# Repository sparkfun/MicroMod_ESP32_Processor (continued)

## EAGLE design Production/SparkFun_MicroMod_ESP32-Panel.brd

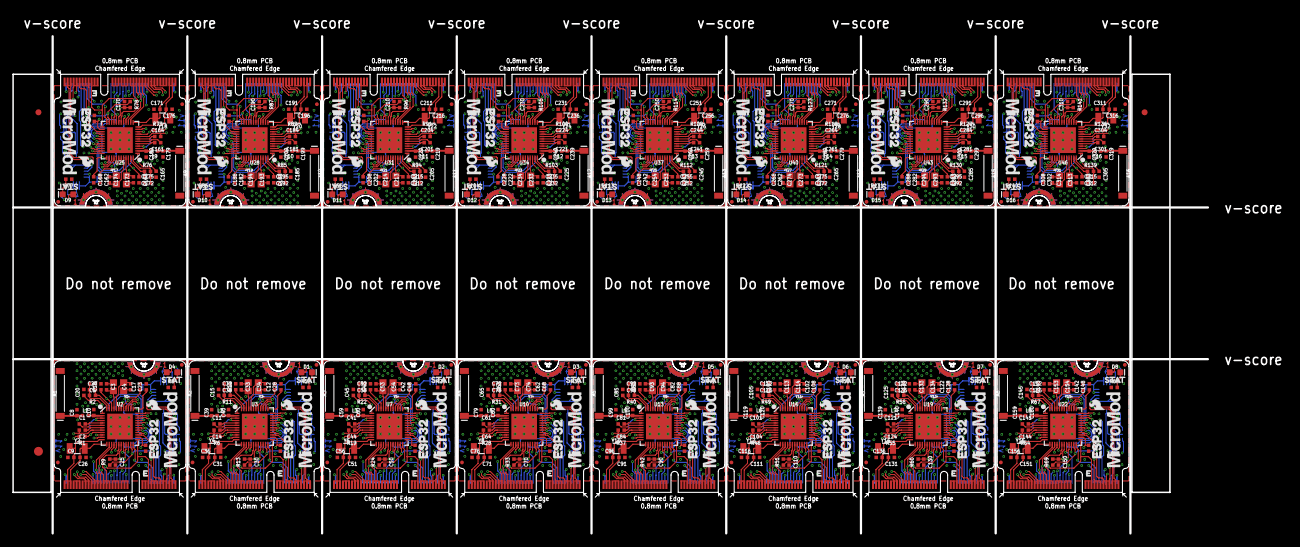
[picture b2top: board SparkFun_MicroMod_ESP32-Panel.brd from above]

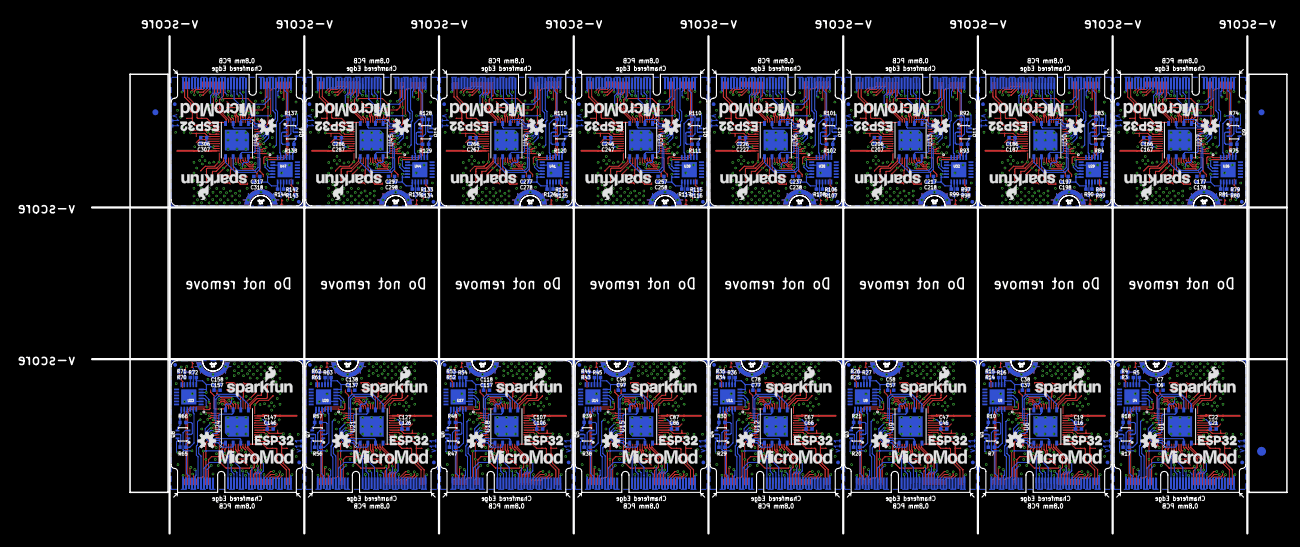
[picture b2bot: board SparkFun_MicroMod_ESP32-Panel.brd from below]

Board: 4 copper layers, 199.6 x 83.1 mm, 822 parts (291 on the bottom side), 864 nets.

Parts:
A1, A2, A3, A4, A5, A6, A7, A8, A9, A10, A11, A12, A13, A14, A15, A16: ANT-2.4GHZ-8.0X1.0MM
C1, C2, C11, C14, C41, C44, C61, C64, C81, C84, C101, C104, C121, C124, C141, C144, C161, C164, C181, C184, C201, C204, C221, C224, C241, C244, C261, C264, C281, C284, C301, C304: 270pF; 0402-TIGHT
C3, C4, C33, C34, C53, C54, C73, C74, C93, C94, C113, C114, C133, C134, C153, C154, C173, C174, C193, C194, C213, C214, C233, C234, C253, C254, C273, C274, C293, C294, C313, C314: 12pF; 0402-TIGHT
C5, C35, C55, C75, C95, C115, C135, C155, C175, C195, C215, C235, C255, C275, C295, C315: 10nF; 0402-TIGHT
C6, C12, C15, C16, C17, C20, C21, C23, C25, C28, C30, C37, C42, C45, C46, C48, C50, C57, C62, C65, C66, C68, C70, C77, C82, C85, C86, C88, C90, C97, C102, C105, C106, C108, C110, C117, C122, C125, C126, C128, C130, C137, C142, C145, C146, C148, C150, C157, C162, C165, C166, C168, C170, C177, C182, C185, C186, C188, C190, C197, C202, C205, C206, C208, C210, C217, C222, C225, C226, C228, C230, C237, C242, C245, C246, C248, C250, C257, C262, C265, C266, C268, C270, C277, C282, C285, C286, C288, C290, C297, C302, C305, C306, C308, C310, C317: 0.1uF; 0402-TIGHT
C7, C38, C58, C78, C98, C118, C138, C158, C178, C198, C218, C238, C258, C278, C298, C318: 4.7uF; 0402-TIGHT
C8, C10, C39, C40, C59, C60, C79, C80, C99, C100, C119, C120, C139, C140, C159, C160, C179, C180, C199, C200, C219, C220, C239, C240, C259, C260, C279, C280, C299, C300, C319, C320: DNP; 0402-TIGHT
C9, C26, C31, C36, C51, C56, C71, C76, C91, C96, C111, C116, C131, C136, C151, C156, C171, C176, C191, C196, C211, C216, C231, C236, C251, C256, C271, C276, C291, C296, C311, C316: 15pF; 0402-TIGHT
C13, C18, C43, C63, C83, C103, C123, C143, C163, C183, C203, C223, C243, C263, C283, C303: 100pF; 0402-TIGHT
C19, C22, C47, C67, C87, C107, C127, C147, C167, C187, C207, C227, C247, C267, C287, C307: 10uF; 0402-TIGHT
C24, C29, C49, C69, C89, C109, C129, C149, C169, C189, C209, C229, C249, C269, C289, C309: 1.0uF; 0402-TIGHT
C27, C32, C52, C72, C92, C112, C132, C152, C172, C192, C212, C232, C252, C272, C292, C312: 3.0nF; 0402-TIGHT
D1, D2, D3, D4, D5, D6, D7, D8, D9, D10, D11, D12, D13, D14, D15, D16: BLUE; LED-0603
E$1, E$2, E$3, E$4: FIDUCIAL-1X2
E$5, E$6: FIDUCIAL-1.5X3
FD1, FD2, FD3, FD4, FD5, FD6, FD7, FD8, FD9, FD10, FD11, FD12, FD13, FD14, FD15, FD16, FD17, FD18, FD19, FD20, FD21, FD22, FD23, FD24, FD25, FD26, FD27, FD28, FD29, FD30, FD31, FD32, FD33, FD34, FD35, FD36, FD37, FD38, FD39, FD40, FD41, FD42, FD43, FD44, FD45, FD46, FD47, FD48, FD49, FD50, FD51, FD52, FD53, FD54, FD55, FD56, FD57, FD58, FD59, FD60, FD61, FD62, FD63, FD64: FIDUCIALUFIDUCIAL; FIDUCIAL-MICRO
J1, J2, J3, J4, J5, J6, J7, J8, J9, J10, J11, J12, J13, J14, J15, J16: MICROMOD-2222; M.2-CARD-E-22
L1, L2, L3, L4, L5, L6, L7, L8, L9, L10, L11, L12, L13, L14, L15, L16: 0; 0402-TIGHT
LOGO1, LOGO2, LOGO5, LOGO7, LOGO9, LOGO11, LOGO13, LOGO15, LOGO17, LOGO19, LOGO21, LOGO23, LOGO25, LOGO27, LOGO29, LOGO31: SFE_LOGO_NAME_FLAME.1_INCH; SFE_LOGO_NAME_FLAME_.1
LOGO3, LOGO4, LOGO6, LOGO8, LOGO10, LOGO12, LOGO14, LOGO16, LOGO18, LOGO20, LOGO22, LOGO24, LOGO26, LOGO28, LOGO30, LOGO32: OSHW-LOGOS; OSHW-LOGO-S
Q1, Q2, Q3, Q4, Q5, Q6, Q7, Q8, Q9, Q10, Q11, Q12, Q13, Q14, Q15, Q16: MBT3904DW1T1; SC70-6
R1, R6, R7, R9, R10, R13, R17, R18, R19, R20, R21, R24, R28, R29, R30, R33, R37, R38, R39, R42, R46, R47, R48, R51, R55, R56, R57, R60, R64, R65, R66, R69, R73, R74, R75, R78, R82, R83, R84, R87, R91, R92, R93, R96, R100, R101, R102, R105, R109, R110, R111, R114, R118, R119, R120, R123, R127, R128, R129, R132, R136, R137, R138, R141: 10k; 0402-TIGHT
R2, R11, R22, R31, R40, R49, R58, R67, R76, R85, R94, R103, R112, R121, R130, R139: 20k; 0402-TIGHT
R3, R14, R25, R34, R43, R52, R61, R70, R79, R88, R97, R106, R115, R124, R133, R142: 22k; 0402-TIGHT
R4, R15, R26, R35, R44, R53, R62, R71, R80, R89, R98, R107, R116, R125, R134, R143: 33k; 0402-TIGHT
R5, R16, R27, R36, R45, R54, R63, R72, R81, R90, R99, R108, R117, R126, R135, R144: 2.2k; 0402-TIGHT
R8, R12, R23, R32, R41, R50, R59, R68, R77, R86, R95, R104, R113, R122, R131, R140: 1k; 0402-TIGHT
U1, U6, U9, U12, U15, U18, U21, U24, U27, U30, U33, U36, U39, U42, U45, U48: W25QXX128MBIT-6X5; WSON-8-6X5
U2, U3, U7, U10, U13, U16, U19, U22, U25, U28, U31, U34, U37, U40, U43, U46: ESP32; QFN48-0.4MM
U4, U5, U8, U11, U14, U17, U20, U23, U26, U29, U32, U35, U38, U41, U44, U47: CP210X; QFN24
U$1, U$5, U$13, U$19, U$25, U$31, U$37, U$43, U$49, U$55, U$61, U$67, U$73, U$79, U$85, U$91: STAT0
U$2, U$6, U$9, U$11, U$15, U$17, U$21, U$23, U$27, U$29, U$33, U$35, U$39, U$41, U$45, U$47, U$51, U$53, U$57, U$59, U$63, U$65, U$69, U$71, U$75, U$77, U$81, U$83, U$87, U$89, U$93, U$95: MICROMOD_LOGO_.5
U$3, U$7, U$8, U$12, U$14, U$18, U$20, U$24, U$26, U$30, U$32, U$36, U$38, U$42, U$44, U$48, U$50, U$54, U$56, U$60, U$62, U$66, U$68, U$72, U$74, U$78, U$80, U$84, U$86, U$90, U$92, U$96: ESP321
U$4, U$10, U$16, U$22, U$28, U$34, U$40, U$46, U$52, U$58, U$64, U$70, U$76, U$82, U$88, U$94: SFE_LOGO_FLAME_.1
Y1, Y3, Y5, Y7, Y9, Y11, Y13, Y15, Y17, Y19, Y21, Y23, Y25, Y27, Y29, Y31: 40MHz; CRYSTAL-SMD-2X2.5MM
Y2, Y4, Y6, Y8, Y10, Y12, Y14, Y16, Y18, Y20, Y22, Y24, Y26, Y28, Y30, Y32: 32.768kHz; CRYSTAL-SMD-3.2X1.5MM

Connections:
0-!BOOT!: J1.11, Q2.6, R9.1, U2.23
0-!BOOT!1: J2.11, Q1.6, R13.1, U3.23
0-!BOOT!2: J3.11, Q3.6, R24.1, U7.23
0-!BOOT!3: J4.11, Q4.6, R33.1, U10.23
0-!BOOT!4: J5.11, Q5.6, R42.1, U13.23
0-!BOOT!5: J6.11, Q6.6, R51.1, U16.23
0-!BOOT!6: J7.11, Q7.6, R60.1, U19.23
0-!BOOT!7: J8.11, Q8.6, R69.1, U22.23
0-!BOOT!8: J9.11, Q9.6, R78.1, U25.23
0-!BOOT!9: J10.11, Q10.6, R87.1, U28.23
0-!BOOT!10: J11.11, Q11.6, R96.1, U31.23
0-!BOOT!11: J12.11, Q12.6, R105.1, U34.23
0-!BOOT!12: J13.11, Q13.6, R114.1, U37.23
0-!BOOT!13: J14.11, Q14.6, R123.1, U40.23
0-!BOOT!14: J15.11, Q15.6, R132.1, U43.23
0-!BOOT!15: J16.11, Q16.6, R141.1, U46.23
1: C14.1, U3.7
2: C11.2, U3.5
2-STAT_LED: D4.A, U2.22
2-STAT_LED1: D1.A, U3.22
2-STAT_LED2: D2.A, U7.22
2-STAT_LED3: D3.A, U10.22
2-STAT_LED4: D5.A, U13.22
2-STAT_LED5: D6.A, U16.22
2-STAT_LED6: D7.A, U19.22
2-STAT_LED7: D8.A, U22.22
2-STAT_LED8: D9.A, U25.22
2-STAT_LED9: D10.A, U28.22
2-STAT_LED10: D11.A, U31.22
2-STAT_LED11: D12.A, U34.22
2-STAT_LED12: D13.A, U37.22
2-STAT_LED13: D14.A, U40.22
2-STAT_LED14: D15.A, U43.22
2-STAT_LED15: D16.A, U46.22
3: C11.1, U3.6
3.3V: C6.1, C7.1, C18.1, C20.1, C21.1, C22.1, C23.1, C25.1, J1.2, J1.74, R1.2, R5.2, R9.2, U2.1, U2.3, U2.4, U2.19, U2.37, U2.43, U2.46, U4.5, U4.6, U4.7
3.3V1: C13.1, C15.1, C16.1, C19.1, C28.1, C30.1, C37.1, C38.1, J2.2, J2.74, R6.2, R13.2, R16.2, U3.1, U3.3, U3.4, U3.19, U3.37, U3.43, U3.46, U5.5, U5.6, U5.7
3.3V2: C43.1, C45.1, C46.1, C47.1, C48.1, C50.1, C57.1, C58.1, J3.2, J3.74, R19.2, R24.2, R27.2, U7.1, U7.3, U7.4, U7.19, U7.37, U7.43, U7.46, U8.5, U8.6, U8.7
3.3V3: C63.1, C65.1, C66.1, C67.1, C68.1, C70.1, C77.1, C78.1, J4.2, J4.74, R28.2, R33.2, R36.2, U10.1, U10.3, U10.4, U10.19, U10.37, U10.43, U10.46, U11.5, U11.6, U11.7
3.3V4: C83.1, C85.1, C86.1, C87.1, C88.1, C90.1, C97.1, C98.1, J5.2, J5.74, R37.2, R42.2, R45.2, U13.1, U13.3, U13.4, U13.19, U13.37, U13.43, U13.46, U14.5, U14.6, U14.7
3.3V5: C103.1, C105.1, C106.1, C107.1, C108.1, C110.1, C117.1, C118.1, J6.2, J6.74, R46.2, R51.2, R54.2, U16.1, U16.3, U16.4, U16.19, U16.37, U16.43, U16.46, U17.5, U17.6, U17.7
3.3V6: C123.1, C125.1, C126.1, C127.1, C128.1, C130.1, C137.1, C138.1, J7.2, J7.74, R55.2, R60.2, R63.2, U19.1, U19.3, U19.4, U19.19, U19.37, U19.43, U19.46, U20.5, U20.6, U20.7
3.3V7: C143.1, C145.1, C146.1, C147.1, C148.1, C150.1, C157.1, C158.1, J8.2, J8.74, R64.2, R69.2, R72.2, U22.1, U22.3, U22.4, U22.19, U22.37, U22.43, U22.46, U23.5, U23.6, U23.7
3.3V8: C163.1, C165.1, C166.1, C167.1, C168.1, C170.1, C177.1, C178.1, J9.2, J9.74, R73.2, R78.2, R81.2, U25.1, U25.3, U25.4, U25.19, U25.37, U25.43, U25.46, U26.5, U26.6, U26.7
3.3V9: C183.1, C185.1, C186.1, C187.1, C188.1, C190.1, C197.1, C198.1, J10.2, J10.74, R82.2, R87.2, R90.2, U28.1, U28.3, U28.4, U28.19, U28.37, U28.43, U28.46, U29.5, U29.6, U29.7
3.3V10: C203.1, C205.1, C206.1, C207.1, C208.1, C210.1, C217.1, C218.1, J11.2, J11.74, R91.2, R96.2, R99.2, U31.1, U31.3, U31.4, U31.19, U31.37, U31.43, U31.46, U32.5, U32.6, U32.7
3.3V11: C223.1, C225.1, C226.1, C227.1, C228.1, C230.1, C237.1, C238.1, J12.2, J12.74, R100.2, R105.2, R108.2, U34.1, U34.3, U34.4, U34.19, U34.37, U34.43, U34.46, U35.5, U35.6, U35.7
3.3V12: C243.1, C245.1, C246.1, C247.1, C248.1, C250.1, C257.1, C258.1, J13.2, J13.74, R109.2, R114.2, R117.2, U37.1, U37.3, U37.4, U37.19, U37.37, U37.43, U37.46, U38.5, U38.6, U38.7
3.3V13: C263.1, C265.1, C266.1, C267.1, C268.1, C270.1, C277.1, C278.1, J14.2, J14.74, R118.2, R123.2, R126.2, U40.1, U40.3, U40.4, U40.19, U40.37, U40.43, U40.46, U41.5, U41.6, U41.7
3.3V14: C283.1, C285.1, C286.1, C287.1, C288.1, C290.1, C297.1, C298.1, J15.2, J15.74, R127.2, R132.2, R135.2, U43.1, U43.3, U43.4, U43.19, U43.37, U43.43, U43.46, U44.5, U44.6, U44.7
3.3V15: C303.1, C305.1, C306.1, C307.1, C308.1, C310.1, C317.1, C318.1, J16.2, J16.74, R136.2, R141.2, R144.2, U46.1, U46.3, U46.4, U46.19, U46.37, U46.43, U46.46, U47.5, U47.6, U47.7
4: C44.1, U7.7
4-I2C_!INT: J1.16, U2.24
4-I2C_!INT1: J2.16, U3.24
4-I2C_!INT2: J3.16, U7.24
4-I2C_!INT3: J4.16, U10.24
4-I2C_!INT4: J5.16, U13.24
4-I2C_!INT5: J6.16, U16.24
4-I2C_!INT6: J7.16, U19.24
4-I2C_!INT7: J8.16, U22.24
4-I2C_!INT8: J9.16, U25.24
4-I2C_!INT9: J10.16, U28.24
4-I2C_!INT10: J11.16, U31.24
4-I2C_!INT11: J12.16, U34.24
4-I2C_!INT12: J13.16, U37.24
4-I2C_!INT13: J14.16, U40.24
4-I2C_!INT14: J15.16, U43.24
4-I2C_!INT15: J16.16, U46.24
5: C41.2, U7.5
5-!CS: J1.55, U2.34
5-!CS1: J2.55, U3.34
5-!CS2: J3.55, U7.34
5-!CS3: J4.55, U10.34
5-!CS4: J5.55, U13.34
5-!CS5: J6.55, U16.34
5-!CS6: J7.55, U19.34
5-!CS7: J8.55, U22.34
5-!CS8: J9.55, U25.34
5-!CS9: J10.55, U28.34
5-!CS10: J11.55, U31.34
5-!CS11: J12.55, U34.34
5-!CS12: J13.55, U37.34
5-!CS13: J14.55, U40.34
5-!CS14: J15.55, U43.34
5-!CS15: J16.55, U46.34
6: C41.1, U7.6
7: C64.1, U10.7
8: C61.2, U10.5
9: C61.1, U10.6
10: C84.1, U13.7
11: C81.2, U13.5
12: C81.1, U13.6
12-PWM1: J1.47, U2.18
12-PWM2: J2.47, U3.18
12-PWM3: J3.47, U7.18
12-PWM4: J4.47, U10.18
12-PWM5: J5.47, U13.18
12-PWM6: J6.47, U16.18
12-PWM7: J7.47, U19.18
12-PWM8: J8.47, U22.18
12-PWM9: J9.47, U25.18
12-PWM10: J10.47, U28.18
12-PWM11: J11.47, U31.18
12-PWM12: J12.47, U34.18
12-PWM13: J13.47, U37.18
12-PWM14: J14.47, U40.18
12-PWM15: J15.47, U43.18
12-PWM16: J16.47, U46.18
13: C104.1, U16.7
13-PWM0: J1.32, U2.20
13-PWM1: J2.32, U3.20
13-PWM2: J3.32, U7.20
13-PWM3: J4.32, U10.20
13-PWM4: J5.32, U13.20
13-PWM5: J6.32, U16.20
13-PWM6: J7.32, U19.20
13-PWM7: J8.32, U22.20
13-PWM8: J9.32, U25.20
13-PWM9: J10.32, U28.20
13-PWM10: J11.32, U31.20
13-PWM11: J12.32, U34.20
13-PWM12: J13.32, U37.20
13-PWM13: J14.32, U40.20
13-PWM14: J15.32, U43.20
13-PWM15: J16.32, U46.20
14: C101.2, U16.5
14-D0: J1.10, U2.17
14-D1: J2.10, U3.17
14-D2: J3.10, U7.17
14-D3: J4.10, U10.17
14-D4: J5.10, U13.17
14-D5: J6.10, U16.17
14-D6: J7.10, U19.17
14-D7: J8.10, U22.17
14-D8: J9.10, U25.17
14-D9: J10.10, U28.17
14-D10: J11.10, U31.17
14-D11: J12.10, U34.17
14-D12: J13.10, U37.17
14-D13: J14.10, U40.17
14-D14: J15.10, U43.17
14-D15: J16.10, U46.17
15: C101.1, U16.6
15-G0: J1.40, U2.21
15-G1: J2.40, U3.21
15-G2: J3.40, U7.21
15-G3: J4.40, U10.21
15-G4: J5.40, U13.21
15-G5: J6.40, U16.21
15-G6: J7.40, U19.21
15-G7: J8.40, U22.21
15-G8: J9.40, U25.21
15-G9: J10.40, U28.21
15-G10: J11.40, U31.21
15-G11: J12.40, U34.21
15-G12: J13.40, U37.21
15-G13: J14.40, U40.21
15-G14: J15.40, U43.21
15-G15: J16.40, U46.21
16: C124.1, U19.7
16-G4/RX1/AUD_IN: J1.19, J1.48, J1.54, U2.25
16-G4/RX1/AUD_IN1: J2.19, J2.48, J2.54, U3.25
16-G4/RX1/AUD_IN2: J3.19, J3.48, J3.54, U7.25
16-G4/RX1/AUD_IN3: J4.19, J4.48, J4.54, U10.25
16-G4/RX1/AUD_IN4: J5.19, J5.48, J5.54, U13.25
16-G4/RX1/AUD_IN5: J6.19, J6.48, J6.54, U16.25
16-G4/RX1/AUD_IN6: J7.19, J7.48, J7.54, U19.25
16-G4/RX1/AUD_IN7: J8.19, J8.48, J8.54, U22.25
16-G4/RX1/AUD_IN8: J9.19, J9.48, J9.54, U25.25
16-G4/RX1/AUD_IN9: J10.19, J10.48, J10.54, U28.25
16-G4/RX1/AUD_IN10: J11.19, J11.48, J11.54, U31.25
16-G4/RX1/AUD_IN11: J12.19, J12.48, J12.54, U34.25
16-G4/RX1/AUD_IN12: J13.19, J13.48, J13.54, U37.25
16-G4/RX1/AUD_IN13: J14.19, J14.48, J14.54, U40.25
16-G4/RX1/AUD_IN14: J15.19, J15.48, J15.54, U43.25
16-G4/RX1/AUD_IN15: J16.19, J16.48, J16.54, U46.25
17: C121.2, U19.5
17-G3/TX1/AUD_OUT: J1.17, J1.46, J1.56, U2.27
17-G3/TX1/AUD_OUT1: J2.17, J2.46, J2.56, U3.27
17-G3/TX1/AUD_OUT2: J3.17, J3.46, J3.56, U7.27
17-G3/TX1/AUD_OUT3: J4.17, J4.46, J4.56, U10.27
17-G3/TX1/AUD_OUT4: J5.17, J5.46, J5.56, U13.27
17-G3/TX1/AUD_OUT5: J6.17, J6.46, J6.56, U16.27
17-G3/TX1/AUD_OUT6: J7.17, J7.46, J7.56, U19.27
17-G3/TX1/AUD_OUT7: J8.17, J8.46, J8.56, U22.27
17-G3/TX1/AUD_OUT8: J9.17, J9.46, J9.56, U25.27
17-G3/TX1/AUD_OUT9: J10.17, J10.46, J10.56, U28.27
17-G3/TX1/AUD_OUT10: J11.17, J11.46, J11.56, U31.27
17-G3/TX1/AUD_OUT11: J12.17, J12.46, J12.56, U34.27
17-G3/TX1/AUD_OUT12: J13.17, J13.46, J13.56, U37.27
17-G3/TX1/AUD_OUT13: J14.17, J14.46, J14.56, U40.27
17-G3/TX1/AUD_OUT14: J15.17, J15.46, J15.56, U43.27
17-G3/TX1/AUD_OUT15: J16.17, J16.46, J16.56, U46.27
18: C121.1, U19.6
18-SCK: J1.57, U2.35
18-SCK1: J2.57, U3.35
18-SCK2: J3.57, U7.35
18-SCK3: J4.57, U10.35
18-SCK4: J5.57, U13.35
18-SCK5: J6.57, U16.35
18-SCK6: J7.57, U19.35
18-SCK7: J8.57, U22.35
18-SCK8: J9.57, U25.35
18-SCK9: J10.57, U28.35
18-SCK10: J11.57, U31.35
18-SCK11: J12.57, U34.35
18-SCK12: J13.57, U37.35
18-SCK13: J14.57, U40.35
18-SCK14: J15.57, U43.35
18-SCK15: J16.57, U46.35
19: C144.1, U22.7
19-CIPO: J1.61, U2.38
19-CIPO1: J2.61, U3.38
19-CIPO2: J3.61, U7.38
19-CIPO3: J4.61, U10.38
19-CIPO4: J5.61, U13.38
19-CIPO5: J6.61, U16.38
19-CIPO6: J7.61, U19.38
19-CIPO7: J8.61, U22.38
19-CIPO8: J9.61, U25.38
19-CIPO9: J10.61, U28.38
19-CIPO10: J11.61, U31.38
19-CIPO11: J12.61, U34.38
19-CIPO12: J13.61, U37.38
19-CIPO13: J14.61, U40.38
19-CIPO14: J15.61, U43.38
19-CIPO15: J16.61, U46.38
20: C141.2, U22.5
21: C141.1, U22.6
21-SDA: J1.12, U2.42
21-SDA1: J2.12, U3.42
21-SDA2: J3.12, U7.42
21-SDA3: J4.12, U10.42
21-SDA4: J5.12, U13.42
21-SDA5: J6.12, U16.42
21-SDA6: J7.12, U19.42
21-SDA7: J8.12, U22.42
21-SDA8: J9.12, U25.42
21-SDA9: J10.12, U28.42
21-SDA10: J11.12, U31.42
21-SDA11: J12.12, U34.42
21-SDA12: J13.12, U37.42
21-SDA13: J14.12, U40.42
21-SDA14: J15.12, U43.42
21-SDA15: J16.12, U46.42
22: C164.1, U25.7
22-SCL: J1.14, U2.39
22-SCL1: J2.14, U3.39
22-SCL2: J3.14, U7.39
22-SCL3: J4.14, U10.39
22-SCL4: J5.14, U13.39
22-SCL5: J6.14, U16.39
22-SCL6: J7.14, U19.39
22-SCL7: J8.14, U22.39
22-SCL8: J9.14, U25.39
22-SCL9: J10.14, U28.39
22-SCL10: J11.14, U31.39
22-SCL11: J12.14, U34.39
22-SCL12: J13.14, U37.39
22-SCL13: J14.14, U40.39
22-SCL14: J15.14, U43.39
22-SCL15: J16.14, U46.39
23: C161.2, U25.5
23-COPI: J1.59, U2.36
23-COPI1: J2.59, U3.36
23-COPI2: J3.59, U7.36
23-COPI3: J4.59, U10.36
23-COPI4: J5.59, U13.36
23-COPI5: J6.59, U16.36
23-COPI6: J7.59, U19.36
23-COPI7: J8.59, U22.36
23-COPI8: J9.59, U25.36
23-COPI9: J10.59, U28.36
23-COPI10: J11.59, U31.36
23-COPI11: J12.59, U34.36
23-COPI12: J13.59, U37.36
23-COPI13: J14.59, U40.36
23-COPI14: J15.59, U43.36
23-COPI15: J16.59, U46.36
24: C161.1, U25.6
25: C184.1, U28.7
25-G1/AUD_LRCLK/SCL1: J1.42, J1.52, J1.53, U2.14
25-G1/AUD_LRCLK/SCL2: J2.42, J2.52, J2.53, U3.14
25-G1/AUD_LRCLK/SCL3: J3.42, J3.52, J3.53, U7.14
25-G1/AUD_LRCLK/SCL4: J4.42, J4.52, J4.53, U10.14
25-G1/AUD_LRCLK/SCL5: J5.42, J5.52, J5.53, U13.14
25-G1/AUD_LRCLK/SCL6: J6.42, J6.52, J6.53, U16.14
25-G1/AUD_LRCLK/SCL7: J7.42, J7.52, J7.53, U19.14
25-G1/AUD_LRCLK/SCL8: J8.42, J8.52, J8.53, U22.14
25-G1/AUD_LRCLK/SCL9: J9.42, J9.52, J9.53, U25.14
25-G1/AUD_LRCLK/SCL10: J10.42, J10.52, J10.53, U28.14
25-G1/AUD_LRCLK/SCL11: J11.42, J11.52, J11.53, U31.14
25-G1/AUD_LRCLK/SCL12: J12.42, J12.52, J12.53, U34.14
25-G1/AUD_LRCLK/SCL13: J13.42, J13.52, J13.53, U37.14
25-G1/AUD_LRCLK/SCL14: J14.42, J14.52, J14.53, U40.14
25-G1/AUD_LRCLK/SCL15: J15.42, J15.52, J15.53, U43.14
25-G1/AUD_LRCLK/SCL16: J16.42, J16.52, J16.53, U46.14
26: C181.2, U28.5
26-G2/AUD_BCLK/SDA1: J1.44, J1.50, J1.51, U2.15
26-G2/AUD_BCLK/SDA2: J2.44, J2.50, J2.51, U3.15
26-G2/AUD_BCLK/SDA3: J3.44, J3.50, J3.51, U7.15
26-G2/AUD_BCLK/SDA4: J4.44, J4.50, J4.51, U10.15
26-G2/AUD_BCLK/SDA5: J5.44, J5.50, J5.51, U13.15
26-G2/AUD_BCLK/SDA6: J6.44, J6.50, J6.51, U16.15
26-G2/AUD_BCLK/SDA7: J7.44, J7.50, J7.51, U19.15
26-G2/AUD_BCLK/SDA8: J8.44, J8.50, J8.51, U22.15
26-G2/AUD_BCLK/SDA9: J9.44, J9.50, J9.51, U25.15
26-G2/AUD_BCLK/SDA10: J10.44, J10.50, J10.51, U28.15
26-G2/AUD_BCLK/SDA11: J11.44, J11.50, J11.51, U31.15
26-G2/AUD_BCLK/SDA12: J12.44, J12.50, J12.51, U34.15
26-G2/AUD_BCLK/SDA13: J13.44, J13.50, J13.51, U37.15
26-G2/AUD_BCLK/SDA14: J14.44, J14.50, J14.51, U40.15
26-G2/AUD_BCLK/SDA15: J15.44, J15.50, J15.51, U43.15
26-G2/AUD_BCLK/SDA16: J16.44, J16.50, J16.51, U46.15
27: C181.1, U28.6
27-D1: J1.18, U2.16
27-D2: J2.18, U3.16
27-D3: J3.18, U7.16
27-D4: J4.18, U10.16
27-D5: J5.18, U13.16
27-D6: J6.18, U16.16
27-D7: J7.18, U19.16
27-D8: J8.18, U22.16
27-D9: J9.18, U25.16
27-D10: J10.18, U28.16
27-D11: J11.18, U31.16
27-D12: J12.18, U34.16
27-D13: J13.18, U37.16
27-D14: J14.18, U40.16
27-D15: J15.18, U43.16
27-D16: J16.18, U46.16
28: C204.1, U31.7
29: C201.2, U31.5
30: C201.1, U31.6
31: C224.1, U34.7
32: C221.2, U34.5
32-G5/RTC: C9.2, J1.73, U2.12, Y2.P$1
32-G5/RTC1: C36.2, J2.73, U3.12, Y4.P$1
32-G5/RTC2: C56.2, J3.73, U7.12, Y6.P$1
32-G5/RTC3: C76.2, J4.73, U10.12, Y8.P$1
32-G5/RTC4: C96.2, J5.73, U13.12, Y10.P$1
32-G5/RTC5: C116.2, J6.73, U16.12, Y12.P$1
32-G5/RTC6: C136.2, J7.73, U19.12, Y14.P$1
32-G5/RTC7: C156.2, J8.73, U22.12, Y16.P$1
32-G5/RTC8: C176.2, J9.73, U25.12, Y18.P$1
32-G5/RTC9: C196.2, J10.73, U28.12, Y20.P$1
32-G5/RTC10: C216.2, J11.73, U31.12, Y22.P$1
32-G5/RTC11: C236.2, J12.73, U34.12, Y24.P$1
32-G5/RTC12: C256.2, J13.73, U37.12, Y26.P$1
32-G5/RTC13: C276.2, J14.73, U40.12, Y28.P$1
32-G5/RTC14: C296.2, J15.73, U43.12, Y30.P$1
32-G5/RTC15: C316.2, J16.73, U46.12, Y32.P$1
33: C221.1, U34.6
33-G6/RTC: C26.2, J1.71, U2.13, Y2.P$2
33-G6/RTC1: C31.2, J2.71, U3.13, Y4.P$2
33-G6/RTC2: C51.2, J3.71, U7.13, Y6.P$2
33-G6/RTC3: C71.2, J4.71, U10.13, Y8.P$2
33-G6/RTC4: C91.2, J5.71, U13.13, Y10.P$2
33-G6/RTC5: C111.2, J6.71, U16.13, Y12.P$2
33-G6/RTC6: C131.2, J7.71, U19.13, Y14.P$2
33-G6/RTC7: C151.2, J8.71, U22.13, Y16.P$2
33-G6/RTC8: C171.2, J9.71, U25.13, Y18.P$2
33-G6/RTC9: C191.2, J10.71, U28.13, Y20.P$2
33-G6/RTC10: C211.2, J11.71, U31.13, Y22.P$2
33-G6/RTC11: C231.2, J12.71, U34.13, Y24.P$2
33-G6/RTC12: C251.2, J13.71, U37.13, Y26.P$2
33-G6/RTC13: C271.2, J14.71, U40.13, Y28.P$2
33-G6/RTC14: C291.2, J15.71, U43.13, Y30.P$2
33-G6/RTC15: C311.2, J16.71, U46.13, Y32.P$2
34: C244.1, U37.7
34-A0: J1.34, U2.10
34-A1: J2.34, U3.10
34-A2: J3.34, U7.10
34-A3: J4.34, U10.10
34-A4: J5.34, U13.10
34-A5: J6.34, U16.10
34-A6: J7.34, U19.10
34-A7: J8.34, U22.10
34-A8: J9.34, U25.10
34-A9: J10.34, U28.10
34-A10: J11.34, U31.10
34-A11: J12.34, U34.10
34-A12: J13.34, U37.10
34-A13: J14.34, U40.10
34-A14: J15.34, U43.10
34-A15: J16.34, U46.10
35: C241.2, U37.5
35-A1: J1.38, U2.11
35-A2: J2.38, U3.11
35-A3: J3.38, U7.11
35-A4: J4.38, U10.11
35-A5: J5.38, U13.11
35-A6: J6.38, U16.11
35-A7: J7.38, U19.11
35-A8: J8.38, U22.11
35-A9: J9.38, U25.11
35-A10: J10.38, U28.11
35-A11: J11.38, U31.11
35-A12: J12.38, U34.11
35-A13: J13.38, U37.11
35-A14: J14.38, U40.11
35-A15: J15.38, U43.11
35-A16: J16.38, U46.11
36: C1.2, U2.5
37: C1.1, U2.6
38: C2.1, U2.7
39: C241.1, U37.6
39-BATT/1: C14.2, J2.49, U3.8
39-BATT/2: C44.2, J3.49, U7.8
39-BATT/3: C2.2, J1.49, U2.8
39-BATT/4: C64.2, J4.49, U10.8
39-BATT/5: C84.2, J5.49, U13.8
39-BATT/6: C104.2, J6.49, U16.8
39-BATT/7: C124.2, J7.49, U19.8
39-BATT/8: C144.2, J8.49, U22.8
39-BATT/9: C164.2, J9.49, U25.8
39-BATT/10: C184.2, J10.49, U28.8
39-BATT/11: C204.2, J11.49, U31.8
39-BATT/12: C224.2, J12.49, U34.8
39-BATT/13: C244.2, J13.49, U37.8
39-BATT/14: C264.2, J14.49, U40.8
39-BATT/15: C284.2, J15.49, U43.8
39-BATT/16: C304.2, J16.49, U46.8
40: C264.1, U40.7
41: C261.2, U40.5
42: C261.1, U40.6
43: C284.1, U43.7
44: C281.2, U43.5
45: C281.1, U43.6
46: C304.1, U46.7
47: C301.2, U46.5
48: C301.1, U46.6
!RESET: J1.6, Q2.3, R1.1, U2.9
!RESET1: J2.6, Q1.3, R6.1, U3.9
!RESET2: J3.6, Q3.3, R19.1, U7.9
!RESET3: J4.6, Q4.3, R28.1, U10.9
!RESET4: J5.6, Q5.3, R37.1, U13.9
!RESET5: J6.6, Q6.3, R46.1, U16.9
!RESET6: J7.6, Q7.3, R55.1, U19.9
!RESET7: J8.6, Q8.3, R64.1, U22.9
!RESET8: J9.6, Q9.3, R73.1, U25.9
!RESET9: J10.6, Q10.3, R82.1, U28.9
!RESET10: J11.6, Q11.3, R91.1, U31.9
!RESET11: J12.6, Q12.3, R100.1, U34.9
!RESET12: J13.6, Q13.3, R109.1, U37.9
!RESET13: J14.6, Q14.3, R118.1, U40.9
!RESET14: J15.6, Q15.3, R127.1, U43.9
!RESET15: J16.6, Q16.3, R136.1, U46.9
CAP_10N: C5.2, C27.1, R2.2, U2.48
CAP_10N1: C32.1, C35.2, R11.2, U3.48
CAP_10N2: C52.1, C55.2, R22.2, U7.48
CAP_10N3: C72.1, C75.2, R31.2, U10.48
CAP_10N4: C92.1, C95.2, R40.2, U13.48
CAP_10N5: C112.1, C115.2, R49.2, U16.48
CAP_10N6: C132.1, C135.2, R58.2, U19.48
CAP_10N7: C152.1, C155.2, R67.2, U22.48
CAP_10N8: C172.1, C175.2, R76.2, U25.48
CAP_10N9: C192.1, C195.2, R85.2, U28.48
CAP_10N10: C212.1, C215.2, R94.2, U31.48
CAP_10N11: C232.1, C235.2, R103.2, U34.48
CAP_10N12: C252.1, C255.2, R112.2, U37.48
CAP_10N13: C272.1, C275.2, R121.2, U40.48
CAP_10N14: C292.1, C295.2, R130.2, U43.48
CAP_10N15: C312.1, C315.2, R139.2, U46.48
D+: J1.3, U4.3
D+1: J2.3, U5.3
D+2: J3.3, U8.3
D+3: J4.3, U11.3
D+4: J5.3, U14.3
D+5: J6.3, U17.3
D+6: J7.3, U20.3
D+7: J8.3, U23.3
D+8: J9.3, U26.3
D+9: J10.3, U29.3
D+10: J11.3, U32.3
D+11: J12.3, U35.3
D+12: J13.3, U38.3
D+13: J14.3, U41.3
D+14: J15.3, U44.3
D+15: J16.3, U47.3
D-: J1.5, U4.4
D-1: J2.5, U5.4
D-2: J3.5, U8.4
D-3: J4.5, U11.4
D-4: J5.5, U14.4
D-5: J6.5, U17.4
D-6: J7.5, U20.4
D-7: J8.5, U23.4
D-8: J9.5, U26.4
D-9: J10.5, U29.4
D-10: J11.5, U32.4
D-11: J12.5, U35.4
D-12: J13.5, U38.4
D-13: J14.5, U41.4
D-14: J15.5, U44.4
D-15: J16.5, U47.4
DTR: Q2.1, R17.1, U4.23
DTR1: Q1.1, R7.1, U5.23
DTR2: Q3.1, R20.1, U8.23
DTR3: Q4.1, R29.1, U11.23
DTR4: Q5.1, R38.1, U14.23
DTR5: Q6.1, R47.1, U17.23
DTR6: Q7.1, R56.1, U20.23
DTR7: Q8.1, R65.1, U23.23
DTR8: Q9.1, R74.1, U26.23
DTR9: Q10.1, R83.1, U29.23
DTR10: Q11.1, R92.1, U32.23
DTR11: Q12.1, R101.1, U35.23
DTR12: Q13.1, R110.1, U38.23
DTR13: Q14.1, R119.1, U41.23
DTR14: Q15.1, R128.1, U44.23
DTR15: Q16.1, R137.1, U47.23
FLASH_SCK: U1.6, U2.31
FLASH_SCK1: U3.31, U6.6
FLASH_SCK2: U7.31, U9.6
FLASH_SCK3: U10.31, U12.6
FLASH_SCK4: U13.31, U15.6
FLASH_SCK5: U16.31, U18.6
FLASH_SCK6: U19.31, U21.6
FLASH_SCK7: U22.31, U24.6
FLASH_SCK8: U25.31, U27.6
FLASH_SCK9: U28.31, U30.6
FLASH_SCK10: U31.31, U33.6
FLASH_SCK11: U34.31, U36.6
FLASH_SCK12: U37.31, U39.6
FLASH_SCK13: U40.31, U42.6
FLASH_SCK14: U43.31, U45.6
FLASH_SCK15: U46.31, U48.6
FLASH_SCS: U1.1, U2.30
FLASH_SCS1: U3.30, U6.1
FLASH_SCS2: U7.30, U9.1
FLASH_SCS3: U10.30, U12.1
FLASH_SCS4: U13.30, U15.1
FLASH_SCS5: U16.30, U18.1
FLASH_SCS6: U19.30, U21.1
FLASH_SCS7: U22.30, U24.1
FLASH_SCS8: U25.30, U27.1
FLASH_SCS9: U28.30, U30.1
FLASH_SCS10: U31.30, U33.1
FLASH_SCS11: U34.30, U36.1
FLASH_SCS12: U37.30, U39.1
FLASH_SCS13: U40.30, U42.1
FLASH_SCS14: U43.30, U45.1
FLASH_SCS15: U46.30, U48.1
FLASH_SDI: U1.5, U2.33
FLASH_SDI1: U3.33, U6.5
FLASH_SDI2: U7.33, U9.5
FLASH_SDI3: U10.33, U12.5
FLASH_SDI4: U13.33, U15.5
FLASH_SDI5: U16.33, U18.5
FLASH_SDI6: U19.33, U21.5
FLASH_SDI7: U22.33, U24.5
FLASH_SDI8: U25.33, U27.5
FLASH_SDI9: U28.33, U30.5
FLASH_SDI10: U31.33, U33.5
FLASH_SDI11: U34.33, U36.5
FLASH_SDI12: U37.33, U39.5
FLASH_SDI13: U40.33, U42.5
FLASH_SDI14: U43.33, U45.5
FLASH_SDI15: U46.33, U48.5
FLASH_SDO: U1.2, U2.32
FLASH_SDO1: U3.32, U6.2
FLASH_SDO2: U7.32, U9.2
FLASH_SDO3: U10.32, U12.2
FLASH_SDO4: U13.32, U15.2
FLASH_SDO5: U16.32, U18.2
FLASH_SDO6: U19.32, U21.2
FLASH_SDO7: U22.32, U24.2
FLASH_SDO8: U25.32, U27.2
FLASH_SDO9: U28.32, U30.2
FLASH_SDO10: U31.32, U33.2
FLASH_SDO11: U34.32, U36.2
FLASH_SDO12: U37.32, U39.2
FLASH_SDO13: U40.32, U42.2
FLASH_SDO14: U43.32, U45.2
FLASH_SDO15: U46.32, U48.2
FLASH_SHD: U1.7, U2.28
FLASH_SHD1: U3.28, U6.7
FLASH_SHD2: U7.28, U9.7
FLASH_SHD3: U10.28, U12.7
FLASH_SHD4: U13.28, U15.7
FLASH_SHD5: U16.28, U18.7
FLASH_SHD6: U19.28, U21.7
FLASH_SHD7: U22.28, U24.7
FLASH_SHD8: U25.28, U27.7
FLASH_SHD9: U28.28, U30.7
FLASH_SHD10: U31.28, U33.7
FLASH_SHD11: U34.28, U36.7
FLASH_SHD12: U37.28, U39.7
FLASH_SHD13: U40.28, U42.7
FLASH_SHD14: U43.28, U45.7
FLASH_SHD15: U46.28, U48.7
FLASH_SWP: U1.3, U2.29
FLASH_SWP1: U3.29, U6.3
FLASH_SWP2: U7.29, U9.3
FLASH_SWP3: U10.29, U12.3
FLASH_SWP4: U13.29, U15.3
FLASH_SWP5: U16.29, U18.3
FLASH_SWP6: U19.29, U21.3
FLASH_SWP7: U22.29, U24.3
FLASH_SWP8: U25.29, U27.3
FLASH_SWP9: U28.29, U30.3
FLASH_SWP10: U31.29, U33.3
FLASH_SWP11: U34.29, U36.3
FLASH_SWP12: U37.29, U39.3
FLASH_SWP13: U40.29, U42.3
FLASH_SWP14: U43.29, U45.3
FLASH_SWP15: U46.29, U48.3
GND: C3.1, C4.1, C5.1, C6.2, C7.2, C8.2, C9.1, C10.2, C17.2, C18.2, C20.2, C21.2, C22.2, C23.2, C24.2, C25.2, C26.1, J1.1, J1.7, J1.33, J1.36, J1.39, J1.45, J1.75, J1.GND1, J1.GND2, J1.GND3, R4.1, R8.1, U1.4, U2.EP, U4.2, U4.PAD, Y1.P2, Y1.P4
GND1: C12.2, C13.2, C15.2, C16.2, C19.2, C28.2, C29.2, C30.2, C31.1, C33.1, C34.1, C35.1, C36.1, C37.2, C38.2, C39.2, C40.2, J2.1, J2.7, J2.33, J2.36, J2.39, J2.45, J2.75, J2.GND1, J2.GND2, J2.GND3, R12.1, R15.1, U3.EP, U5.2, U5.PAD, U6.4, Y3.P2, Y3.P4
GND2: C42.2, C43.2, C45.2, C46.2, C47.2, C48.2, C49.2, C50.2, C51.1, C53.1, C54.1, C55.1, C56.1, C57.2, C58.2, C59.2, C60.2, J3.1, J3.7, J3.33, J3.36, J3.39, J3.45, J3.75, J3.GND1, J3.GND2, J3.GND3, R23.1, R26.1, U7.EP, U8.2, U8.PAD, U9.4, Y5.P2, Y5.P4
GND3: C62.2, C63.2, C65.2, C66.2, C67.2, C68.2, C69.2, C70.2, C71.1, C73.1, C74.1, C75.1, C76.1, C77.2, C78.2, C79.2, C80.2, J4.1, J4.7, J4.33, J4.36, J4.39, J4.45, J4.75, J4.GND1, J4.GND2, J4.GND3, R32.1, R35.1, U10.EP, U11.2, U11.PAD, U12.4, Y7.P2, Y7.P4
GND4: C82.2, C83.2, C85.2, C86.2, C87.2, C88.2, C89.2, C90.2, C91.1, C93.1, C94.1, C95.1, C96.1, C97.2, C98.2, C99.2, C100.2, J5.1, J5.7, J5.33, J5.36, J5.39, J5.45, J5.75, J5.GND1, J5.GND2, J5.GND3, R41.1, R44.1, U13.EP, U14.2, U14.PAD, U15.4, Y9.P2, Y9.P4
GND5: C102.2, C103.2, C105.2, C106.2, C107.2, C108.2, C109.2, C110.2, C111.1, C113.1, C114.1, C115.1, C116.1, C117.2, C118.2, C119.2, C120.2, J6.1, J6.7, J6.33, J6.36, J6.39, J6.45, J6.75, J6.GND1, J6.GND2, J6.GND3, R50.1, R53.1, U16.EP, U17.2, U17.PAD, U18.4, Y11.P2, Y11.P4
GND6: C122.2, C123.2, C125.2, C126.2, C127.2, C128.2, C129.2, C130.2, C131.1, C133.1, C134.1, C135.1, C136.1, C137.2, C138.2, C139.2, C140.2, J7.1, J7.7, J7.33, J7.36, J7.39, J7.45, J7.75, J7.GND1, J7.GND2, J7.GND3, R59.1, R62.1, U19.EP, U20.2, U20.PAD, U21.4, Y13.P2, Y13.P4
GND7: C142.2, C143.2, C145.2, C146.2, C147.2, C148.2, C149.2, C150.2, C151.1, C153.1, C154.1, C155.1, C156.1, C157.2, C158.2, C159.2, C160.2, J8.1, J8.7, J8.33, J8.36, J8.39, J8.45, J8.75, J8.GND1, J8.GND2, J8.GND3, R68.1, R71.1, U22.EP, U23.2, U23.PAD, U24.4, Y15.P2, Y15.P4
GND8: C162.2, C163.2, C165.2, C166.2, C167.2, C168.2, C169.2, C170.2, C171.1, C173.1, C174.1, C175.1, C176.1, C177.2, C178.2, C179.2, C180.2, J9.1, J9.7, J9.33, J9.36, J9.39, J9.45, J9.75, J9.GND1, J9.GND2, J9.GND3, R77.1, R80.1, U25.EP, U26.2, U26.PAD, U27.4, Y17.P2, Y17.P4
GND9: C182.2, C183.2, C185.2, C186.2, C187.2, C188.2, C189.2, C190.2, C191.1, C193.1, C194.1, C195.1, C196.1, C197.2, C198.2, C199.2, C200.2, J10.1, J10.7, J10.33, J10.36, J10.39, J10.45, J10.75, J10.GND1, J10.GND2, J10.GND3, R86.1, R89.1, U28.EP, U29.2, U29.PAD, U30.4, Y19.P2, Y19.P4
GND10: C202.2, C203.2, C205.2, C206.2, C207.2, C208.2, C209.2, C210.2, C211.1, C213.1, C214.1, C215.1, C216.1, C217.2, C218.2, C219.2, C220.2, J11.1, J11.7, J11.33, J11.36, J11.39, J11.45, J11.75, J11.GND1, J11.GND2, J11.GND3, R95.1, R98.1, U31.EP, U32.2, U32.PAD, U33.4, Y21.P2, Y21.P4
GND11: C222.2, C223.2, C225.2, C226.2, C227.2, C228.2, C229.2, C230.2, C231.1, C233.1, C234.1, C235.1, C236.1, C237.2, C238.2, C239.2, C240.2, J12.1, J12.7, J12.33, J12.36, J12.39, J12.45, J12.75, J12.GND1, J12.GND2, J12.GND3, R104.1, R107.1, U34.EP, U35.2, U35.PAD, U36.4, Y23.P2, Y23.P4
GND12: C242.2, C243.2, C245.2, C246.2, C247.2, C248.2, C249.2, C250.2, C251.1, C253.1, C254.1, C255.1, C256.1, C257.2, C258.2, C259.2, C260.2, J13.1, J13.7, J13.33, J13.36, J13.39, J13.45, J13.75, J13.GND1, J13.GND2, J13.GND3, R113.1, R116.1, U37.EP, U38.2, U38.PAD, U39.4, Y25.P2, Y25.P4
GND13: C262.2, C263.2, C265.2, C266.2, C267.2, C268.2, C269.2, C270.2, C271.1, C273.1, C274.1, C275.1, C276.1, C277.2, C278.2, C279.2, C280.2, J14.1, J14.7, J14.33, J14.36, J14.39, J14.45, J14.75, J14.GND1, J14.GND2, J14.GND3, R122.1, R125.1, U40.EP, U41.2, U41.PAD, U42.4, Y27.P2, Y27.P4
GND14: C282.2, C283.2, C285.2, C286.2, C287.2, C288.2, C289.2, C290.2, C291.1, C293.1, C294.1, C295.1, C296.1, C297.2, C298.2, C299.2, C300.2, J15.1, J15.7, J15.33, J15.36, J15.39, J15.45, J15.75, J15.GND1, J15.GND2, J15.GND3, R131.1, R134.1, U43.EP, U44.2, U44.PAD, U45.4, Y29.P2, Y29.P4
GND15: C302.2, C303.2, C305.2, C306.2, C307.2, C308.2, C309.2, C310.2, C311.1, C313.1, C314.1, C315.1, C316.1, C317.2, C318.2, C319.2, C320.2, J16.1, J16.7, J16.33, J16.36, J16.39, J16.45, J16.75, J16.GND1, J16.GND2, J16.GND3, R140.1, R143.1, U46.EP, U47.2, U47.PAD, U48.4, Y31.P2, Y31.P4
unnamed: D4.C, R8.2
unnamed: R3.1, R4.2, U4.8
unnamed: R5.1, U4.9
unnamed: C27.2, R2.1, U2.47
unnamed: A1.FEED, C8.1, L1.1
unnamed: Q1.5, R7.2
unnamed: Q1.2, R10.2
unnamed: C10.1, L1.2, U2.2
unnamed: C33.2, U3.45, Y3.P1
unnamed: Q2.5, R17.2
unnamed: C34.2, U3.44, Y3.P3
unnamed: Q2.2, R18.2
unnamed: C3.2, U2.45, Y1.P1
unnamed: D1.C, R12.2
unnamed: C4.2, U2.44, Y1.P3
unnamed: C32.2, R11.1, U3.47
unnamed: R14.1, R15.2, U5.8
unnamed: R16.1, U5.9
unnamed: A2.FEED, C39.1, L2.1
unnamed: C40.1, L2.2, U3.2
unnamed: Q3.5, R20.2
unnamed: Q3.2, R21.2
unnamed: C53.2, U7.45, Y5.P1
unnamed: C54.2, U7.44, Y5.P3
unnamed: D2.C, R23.2
unnamed: C52.2, R22.1, U7.47
unnamed: R25.1, R26.2, U8.8
unnamed: R27.1, U8.9
unnamed: A3.FEED, C59.1, L3.1
unnamed: C60.1, L3.2, U7.2
unnamed: Q4.5, R29.2
unnamed: Q4.2, R30.2
unnamed: C73.2, U10.45, Y7.P1
unnamed: C74.2, U10.44, Y7.P3
unnamed: D3.C, R32.2
unnamed: C72.2, R31.1, U10.47
unnamed: R34.1, R35.2, U11.8
unnamed: R36.1, U11.9
unnamed: A4.FEED, C79.1, L4.1
unnamed: C80.1, L4.2, U10.2
unnamed: Q5.5, R38.2
unnamed: Q5.2, R39.2
unnamed: C93.2, U13.45, Y9.P1
unnamed: C94.2, U13.44, Y9.P3
unnamed: D5.C, R41.2
unnamed: C92.2, R40.1, U13.47
unnamed: R43.1, R44.2, U14.8
unnamed: R45.1, U14.9
unnamed: A5.FEED, C99.1, L5.1
unnamed: C100.1, L5.2, U13.2
unnamed: Q6.5, R47.2
unnamed: Q6.2, R48.2
unnamed: C113.2, U16.45, Y11.P1
unnamed: C114.2, U16.44, Y11.P3
unnamed: D6.C, R50.2
unnamed: C112.2, R49.1, U16.47
unnamed: R52.1, R53.2, U17.8
unnamed: R54.1, U17.9
unnamed: A6.FEED, C119.1, L6.1
unnamed: C120.1, L6.2, U16.2
unnamed: Q7.5, R56.2
unnamed: Q7.2, R57.2
unnamed: C133.2, U19.45, Y13.P1
unnamed: C134.2, U19.44, Y13.P3
unnamed: D7.C, R59.2
unnamed: C132.2, R58.1, U19.47
unnamed: R61.1, R62.2, U20.8
unnamed: R63.1, U20.9
unnamed: A7.FEED, C139.1, L7.1
unnamed: C140.1, L7.2, U19.2
unnamed: Q8.5, R65.2
unnamed: Q8.2, R66.2
unnamed: C153.2, U22.45, Y15.P1
unnamed: C154.2, U22.44, Y15.P3
unnamed: D8.C, R68.2
unnamed: C152.2, R67.1, U22.47
unnamed: R70.1, R71.2, U23.8
unnamed: R72.1, U23.9
unnamed: A8.FEED, C159.1, L8.1
unnamed: C160.1, L8.2, U22.2
unnamed: Q9.5, R74.2
unnamed: Q9.2, R75.2
unnamed: C173.2, U25.45, Y17.P1
unnamed: C174.2, U25.44, Y17.P3
unnamed: D9.C, R77.2
unnamed: C172.2, R76.1, U25.47
unnamed: R79.1, R80.2, U26.8
unnamed: R81.1, U26.9
unnamed: A9.FEED, C179.1, L9.1
unnamed: C180.1, L9.2, U25.2
unnamed: Q10.5, R83.2
unnamed: Q10.2, R84.2
unnamed: C193.2, U28.45, Y19.P1
unnamed: C194.2, U28.44, Y19.P3
unnamed: D10.C, R86.2
unnamed: C192.2, R85.1, U28.47
unnamed: R88.1, R89.2, U29.8
unnamed: R90.1, U29.9
unnamed: A10.FEED, C199.1, L10.1
unnamed: C200.1, L10.2, U28.2
unnamed: Q11.5, R92.2
unnamed: Q11.2, R93.2
unnamed: C213.2, U31.45, Y21.P1
unnamed: C214.2, U31.44, Y21.P3
unnamed: D11.C, R95.2
unnamed: C212.2, R94.1, U31.47
unnamed: R97.1, R98.2, U32.8
unnamed: R99.1, U32.9
unnamed: A11.FEED, C219.1, L11.1
unnamed: C220.1, L11.2, U31.2
unnamed: Q12.5, R101.2
unnamed: Q12.2, R102.2
unnamed: C233.2, U34.45, Y23.P1
unnamed: C234.2, U34.44, Y23.P3
unnamed: D12.C, R104.2
unnamed: C232.2, R103.1, U34.47
unnamed: R106.1, R107.2, U35.8
unnamed: R108.1, U35.9
unnamed: A12.FEED, C239.1, L12.1
unnamed: C240.1, L12.2, U34.2
unnamed: Q13.5, R110.2
unnamed: Q13.2, R111.2
unnamed: C253.2, U37.45, Y25.P1
unnamed: C254.2, U37.44, Y25.P3
unnamed: D13.C, R113.2
unnamed: C252.2, R112.1, U37.47
unnamed: R115.1, R116.2, U38.8
unnamed: R117.1, U38.9
unnamed: A13.FEED, C259.1, L13.1
unnamed: C260.1, L13.2, U37.2
unnamed: Q14.5, R119.2
unnamed: Q14.2, R120.2
unnamed: C273.2, U40.45, Y27.P1
unnamed: C274.2, U40.44, Y27.P3
unnamed: D14.C, R122.2
unnamed: C272.2, R121.1, U40.47
unnamed: R124.1, R125.2, U41.8
unnamed: R126.1, U41.9
unnamed: A14.FEED, C279.1, L14.1
unnamed: C280.1, L14.2, U40.2
unnamed: Q15.5, R128.2
unnamed: Q15.2, R129.2
unnamed: C293.2, U43.45, Y29.P1
unnamed: C294.2, U43.44, Y29.P3
unnamed: D15.C, R131.2
unnamed: C292.2, R130.1, U43.47
unnamed: R133.1, R134.2, U44.8
unnamed: R135.1, U44.9
unnamed: A15.FEED, C299.1, L15.1
unnamed: C300.1, L15.2, U43.2
unnamed: Q16.5, R137.2
unnamed: Q16.2, R138.2
unnamed: C313.2, U46.45, Y31.P1
unnamed: C314.2, U46.44, Y31.P3
unnamed: D16.C, R140.2
unnamed: C312.2, R139.1, U46.47
unnamed: R142.1, R143.2, U47.8
unnamed: R144.1, U47.9
unnamed: A16.FEED, C319.1, L16.1
unnamed: C320.1, L16.2, U46.2
RTS: Q2.4, R18.1, U4.19
RTS1: Q1.4, R10.1, U5.19
RTS2: Q3.4, R21.1, U8.19
RTS3: Q4.4, R30.1, U11.19
RTS4: Q5.4, R39.1, U14.19
RTS5: Q6.4, R48.1, U17.19
RTS6: Q7.4, R57.1, U20.19
RTS7: Q8.4, R66.1, U23.19
RTS8: Q9.4, R75.1, U26.19
RTS9: Q10.4, R84.1, U29.19
RTS10: Q11.4, R93.1, U32.19
RTS11: Q12.4, R102.1, U35.19
RTS12: Q13.4, R111.1, U38.19
RTS13: Q14.4, R120.1, U41.19
RTS14: Q15.4, R129.1, U44.19
RTS15: Q16.4, R138.1, U47.19
U0RXD: U2.40, U4.21
U0RXD1: U3.40, U5.21
U0RXD2: U7.40, U8.21
U0RXD3: U10.40, U11.21
U0RXD4: U13.40, U14.21
U0RXD5: U16.40, U17.21
U0RXD6: U19.40, U20.21
U0RXD7: U22.40, U23.21
U0RXD8: U25.40, U26.21
U0RXD9: U28.40, U29.21
U0RXD10: U31.40, U32.21
U0RXD11: U34.40, U35.21
U0RXD12: U37.40, U38.21
U0RXD13: U40.40, U41.21
U0RXD14: U43.40, U44.21
U0RXD15: U46.40, U47.21
U0TXD: U2.41, U4.20
U0TXD1: U3.41, U5.20
U0TXD2: U7.41, U8.20
U0TXD3: U10.41, U11.20
U0TXD4: U13.41, U14.20
U0TXD5: U16.41, U17.20
U0TXD6: U19.41, U20.20
U0TXD7: U22.41, U23.20
U0TXD8: U25.41, U26.20
U0TXD9: U28.41, U29.20
U0TXD10: U31.41, U32.20
U0TXD11: U34.41, U35.20
U0TXD12: U37.41, U38.20
U0TXD13: U40.41, U41.20
U0TXD14: U43.41, U44.20
U0TXD15: U46.41, U47.20
VDD: C17.1, C24.1, U1.8, U2.26
VDD1: C12.1, C29.1, U3.26, U6.8
VDD2: C42.1, C49.1, U7.26, U9.8
VDD3: C62.1, C69.1, U10.26, U12.8
VDD4: C82.1, C89.1, U13.26, U15.8
VDD5: C102.1, C109.1, U16.26, U18.8
VDD6: C122.1, C129.1, U19.26, U21.8
VDD7: C142.1, C149.1, U22.26, U24.8
VDD8: C162.1, C169.1, U25.26, U27.8
VDD9: C182.1, C189.1, U28.26, U30.8
VDD10: C202.1, C209.1, U31.26, U33.8
VDD11: C222.1, C229.1, U34.26, U36.8
VDD12: C242.1, C249.1, U37.26, U39.8
VDD13: C262.1, C269.1, U40.26, U42.8
VDD14: C282.1, C289.1, U43.26, U45.8
VDD15: C302.1, C309.1, U46.26, U48.8
V_USB: J1.9, R3.2
V_USB1: J2.9, R14.2
V_USB2: J3.9, R25.2
V_USB3: J4.9, R34.2
V_USB4: J5.9, R43.2
V_USB5: J6.9, R52.2
V_USB6: J7.9, R61.2
V_USB7: J8.9, R70.2
V_USB8: J9.9, R79.2
V_USB9: J10.9, R88.2
V_USB10: J11.9, R97.2
V_USB11: J12.9, R106.2
V_USB12: J13.9, R115.2
V_USB13: J14.9, R124.2
V_USB14: J15.9, R133.2
V_USB15: J16.9, R142.2

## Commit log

2020-05-14 intial commit
2020-05-15 updated Prod_IDs
    Added missing PROD_IDs
    Added Logos to sch
2020-05-21 Updated design
2020-05-21 Fixed RF trace Width
    - Updated RF trace width to 13mil, added calculation to schematic
2020-05-26 v01 silk update
    rotated the silk to line up with carrier boards
2020-06-22 v02
    - Replaced antenna inductor with 0 ohm resistor
    - Replaced Flash IC VDD supply from 3.3V power rail to ESP32's FLASH_VDD pin.
    - Replaced edge connector to updated pinout
2020-06-22 v02 updated top copper
2020-07-29 v10
    - Updated board to v10
    - Removed RX and TX test points
    - Changed Flash_VDD label to VDD power symbol
    - Changed SPI labels to COPI CIPO
    - Added vias below antenna
    - Moved OSHW logo
2020-07-31 Production Files
2020-07-31 Updated ordering instructions
2020-08-17 v10 fix
    Rearranged GPIO pins
    -Boot was removed from I2C_INT
    -GPIO4 was moved from G0 to I2C_INT
    -GPIO12 was moved from G1 to G4
    -Moved GPIO25/26 from G4/5 to G0/1
    -Swapped GPIO16/17 from G2/3 to G3/2
2020-08-17 New panel
2020-08-31 Updated MicroMod Connector Schematic Symbol
2020-09-08 Updated USB to UART
    USB to UART converter can be either the CP2102N or CP2104
2020-09-17 v11
    - Updated to new MicroMod Pinout
    - Changed SCK from 14 to 18
    - Changed SDO from 15 to 23
    - Changed SDI from 2 to 19
    - Changed CS from 13 to 5
    - Changed PWM0 from 18 to 13
2020-09-18 v11 update
    - Added notes to boot strapping pins
    - Added ENIG finish note to tDocu
    - Updated labeling for USB to UART brdige
    - Updated SPI flash labels
2020-09-21 v11 updated inner layers
2020-09-21 v11 Panel
